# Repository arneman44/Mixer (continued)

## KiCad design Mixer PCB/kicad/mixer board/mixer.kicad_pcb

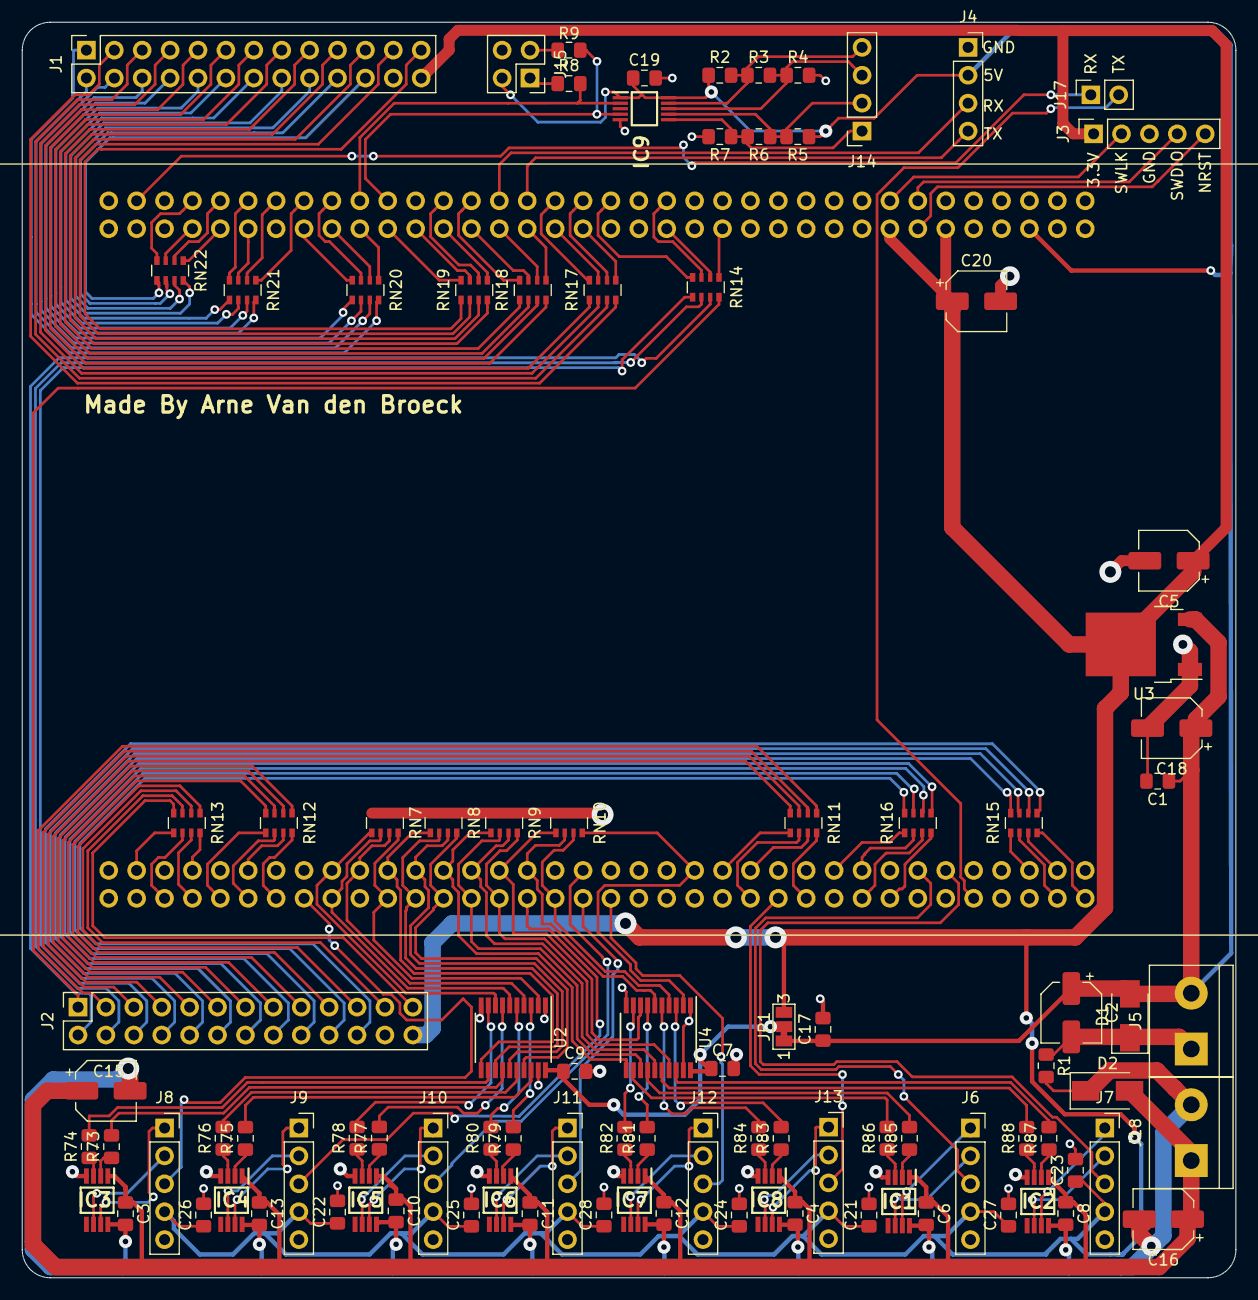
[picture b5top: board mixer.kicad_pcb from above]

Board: 2 copper layers, 110.5 x 114.3 mm, 101 parts (0 on the bottom side), 189 nets.

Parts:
C1, C3, C4, C6, C7, C8, C9, C10, C11, C12, C13, C17, C19, C21, C22, C23, C24, C25, C26, C27, C28: C; C_0805_2012Metric_Pad1.15x1.40mm_HandSolder
C2, C5, C15, C16, C18, C20: CP; CP_Elec_5x5.4
D1, D2: DIODE; D_SMA
IC1, IC2, IC3, IC4, IC5, IC6, IC7, IC8: LB1938FA-BH; SOP65P490X110-8N
IC9: PCA9615DP; SOP50P490X110-10N
J1, J2: Conn_02x13_Odd_Even; PinSocket_2x13_P2.54mm_Vertical
J3, J6, J7, J8, J9, J10, J11, J12, J13: Conn_01x05; PinSocket_1x05_P2.54mm_Vertical
J4: LCD; PinSocket_1x04_P2.54mm_Vertical
J5, J18: Conn_01x02; TerminalBlock_bornier-2_P5.08mm
J14: J; PinSocket_1x04_P2.54mm_Vertical
J15: Conn_02x02_Counter_Clockwise; PinSocket_2x02_P2.54mm_Vertical
J17: Conn_01x02; PinSocket_1x02_P2.54mm_Vertical
JP1: Jumper_3_Bridged12; SolderJumper-3_P1.3mm_Bridged12_Pad1.0x1.5mm_NumberLabels
R1, R8, R9: 4.7K; R_0805_2012Metric_Pad1.15x1.40mm_HandSolder
R2, R4, R5, R7: 390; R_0805_2012Metric_Pad1.15x1.40mm_HandSolder
R3, R6: 100; R_0805_2012Metric_Pad1.15x1.40mm_HandSolder
R73, R74, R75, R76, R77, R78, R79, R80, R81, R82, R83, R84, R85, R86, R87, R88: R; R_0805_2012Metric_Pad1.15x1.40mm_HandSolder
RN7, RN8, RN9, RN10, RN11, RN12, RN13, RN14, RN15, RN16, RN17, RN18, RN19, RN20, RN21, RN22: R_Pack04; R_Array_Convex_4x0603
U1: NUCLEO144-F746ZG; ST_Morpho_Connector_144_STLink_MountingHoles_double
U2, U4: 74HC240; TSSOP-20_4.4x6.5mm_P0.65mm
U3: LD1086DT33TR; TO-252-2

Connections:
+3V3: C5.1, C20.1, C21.1, C22.1, C23.1, C24.1, C25.1, C26.1, C27.1, C28.1, J1.26, J2.26, J3.1, J6.4, J7.4, J8.4, J9.4, J10.4, J11.4, J12.4, J13.4, JP1.3, U1.5, U1.12, U1.16, U1.79, U3.2
+5V: C1.1, C2.1, C17.1, C18.1, C19.1, D1.2, IC9.1, IC9.10, J4.2, J5.2, J15.3, JP1.1, R2.1, R5.1, U1.6, U3.3
Button1: RN14.1, U1.28
Button2: RN11.8, U1.94
Button3: RN11.7, U1.97
Button4: RN11.6, U1.98
Button5: RN11.5, U1.99
Button6: RN12.8, U1.132
Button7: RN12.7, U1.133
Button8: RN12.6, U1.134
Button9: RN14.2, U1.32
Button10: RN14.3, U1.31
Button11: RN14.4, U1.35
Button12: RN15.4, U1.74
Button13: RN15.3, U1.75
Button14: RN15.2, U1.76
Button15: RN15.1, U1.77
Button16: RN16.4, U1.88
DSCL+: IC9.7, J14.2, R5.2, R6.1
DSCL-: IC9.6, J14.1, R6.2, R7.1
DSDA+: IC9.8, J14.3, R3.2, R4.1
DSDA-: IC9.9, J14.4, R2.2, R3.1
Encoder1A: RN20.1, U1.54
Encoder1B: RN17.5, U1.38
Encoder1Button: RN20.2, U1.56
Encoder2A: RN17.6, U1.37
Encoder2B: RN17.7, U1.40
Encoder2Button: RN20.3, U1.55
Encoder3A: RN21.1, U1.57
Encoder3B: RN21.2, U1.59
Encoder3Button: RN20.4, U1.58
Encoder4A: RN18.5, U1.42
Encoder4B: RN18.6, U1.44
Encoder4Button: RN17.8, U1.39
Encoder5A: RN21.3, U1.62
Encoder5B: RN21.4, U1.61
Encoder5Button: RN22.1, U1.64
Encoder6A: RN18.7, U1.46
Encoder6B: RN18.8, U1.45
Encoder6Button: RN22.2, U1.63
Encoder7A: RN19.5, U1.48
Encoder7B: RN19.6, U1.47
Encoder7Button: RN22.3, U1.66
Encoder8A: RN19.7, U1.50
Encoder8B: RN19.8, U1.52
Encoder8Button: RN22.4, U1.65
Fader1: J8.3, U1.130
Fader2: J9.3, U1.114
Fader3: J10.3, U1.109
Fader4: J11.3, U1.110
Fader5: J12.3, U1.108
Fader6: J13.3, U1.96
Fader7: J6.3, U1.85
Fader8: J7.3, U1.83
GND: C1.2, C2.2, C5.2, C7.2, C9.2, C17.2, C18.2, C19.2, C20.2, C21.2, C22.2, C23.2, C24.2, C25.2, C26.2, C27.2, C28.2, D1.1, IC1.4, IC2.4, IC3.4, IC4.4, IC5.4, IC6.4, IC7.4, IC8.4, IC9.5, J1.24, J2.24, J3.3, J4.1, J5.1, J6.5, J7.5, J8.5, J9.5, J10.5, J11.5, J12.5, J13.5, J15.4, R1.1, R4.2, R7.2, RN7.1, RN7.2, RN7.3, RN7.4, RN8.1, RN8.2, RN8.3, RN8.4, RN9.1, RN9.2, RN9.3, RN9.4, RN10.1, RN10.2, RN10.3, RN10.4, U1.8, U1.19, U1.20, U1.22, U1.49, U1.60, U1.71, U1.72, U1.81, U1.92, U1.104, U1.111, U1.126, U1.135, U1.143, U1.144, U2.1, U2.10, U2.19, U3.1, U4.1, U4.10, U4.19
GNDPWR: C3.2, C4.2, C6.2, C8.2, C10.2, C11.2, C12.2, C13.2, C15.2, C16.2, D2.1, IC1.8, IC2.8, IC3.8, IC4.8, IC5.8, IC6.8, IC7.8, IC8.8, J18.2, R1.2
LED1: RN12.5, U1.136
LED2: RN13.8, U1.137
LED3: RN13.7, U1.138
LED4: RN13.6, U1.140
LED5: RN13.5, U1.141
LED6: RN16.3, U1.90
LED7: RN16.2, U1.89
LED8: RN16.1, U1.91
Motor1A: RN7.6, U1.128, U2.6
Motor1A_: R73.2, U2.14
Motor1B: RN7.5, U1.127, U2.8
Motor1B_: R74.2, U2.12
Motor2A: RN7.8, U1.124, U2.2
Motor2A_: R75.2, U2.18
Motor2B: RN7.7, U1.125, U2.4
Motor2B_: R76.2, U2.16
Motor3A: RN8.6, U1.122, U2.13
Motor3A_: R77.2, U2.7
Motor3B: RN8.5, U1.123, U2.11
Motor3B_: R78.2, U2.9
Motor4A: RN8.8, U1.120, U2.17
Motor4A_: R79.2, U2.3
Motor4B: RN8.7, U1.121, U2.15
Motor4B_: R80.2, U2.5
Motor5A: RN9.6, U1.118, U4.13
Motor5A_: R81.2, U4.7
Motor5B: RN9.5, U1.119, U4.11
Motor5B_: R82.2, U4.9
Motor6A: RN9.8, U1.116, U4.17
Motor6A_: R83.2, U4.3
Motor6B: RN9.7, U1.117, U4.15
Motor6B_: R84.2, U4.5
Motor7A: RN10.6, U1.113, U4.6
Motor7A_: R85.2, U4.14
Motor7B: RN10.5, U1.115, U4.8
Motor7B_: R86.2, U4.12
Motor8A: RN10.8, U1.101, U4.2
Motor8A_: R87.2, U4.18
Motor8B: RN10.7, U1.112, U4.4
Motor8B_: R88.2, U4.16
NRST: J3.5, U1.14
unnamed: C7.1, C9.1, JP1.2, U2.20, U4.20
unnamed: IC1.2, R85.1
unnamed: IC1.3, R86.1
unnamed: IC1.6, J6.2
unnamed: IC1.7, J6.1
unnamed: IC2.2, R87.1
unnamed: IC2.3, R88.1
unnamed: IC2.6, J7.2
unnamed: IC2.7, J7.1
unnamed: IC3.2, R73.1
unnamed: IC3.3, R74.1
unnamed: IC3.6, J8.2
unnamed: IC3.7, J8.1
unnamed: IC4.2, R75.1
unnamed: IC4.3, R76.1
unnamed: IC4.6, J9.2
unnamed: IC4.7, J9.1
unnamed: IC5.2, R77.1
unnamed: IC5.3, R78.1
unnamed: IC5.6, J10.2
unnamed: IC5.7, J10.1
unnamed: IC6.2, R79.1
unnamed: IC6.3, R80.1
unnamed: IC6.6, J11.2
unnamed: IC6.7, J11.1
unnamed: IC7.2, R81.1
unnamed: IC7.3, R82.1
unnamed: IC7.6, J12.2
unnamed: IC7.7, J12.1
unnamed: IC8.2, R83.1
unnamed: IC8.3, R84.1
unnamed: IC8.6, J13.2
unnamed: IC8.7, J13.1
unnamed: J1.1, RN20.8
unnamed: J1.2, RN20.7
unnamed: J1.3, RN17.4
unnamed: J1.4, RN20.6
unnamed: J1.5, RN17.3
unnamed: J1.6, RN20.5
unnamed: J1.7, RN17.2
unnamed: J1.8, RN21.8
unnamed: J1.9, RN17.1
unnamed: J1.10, RN21.7
unnamed: J1.11, RN18.4
unnamed: J1.12, RN21.6
unnamed: J1.13, RN18.3
unnamed: J1.14, RN21.5
unnamed: J1.15, RN18.2
unnamed: J1.16, RN22.8
unnamed: J1.17, RN18.1
unnamed: J1.18, RN22.7
unnamed: J1.19, RN19.4
unnamed: J1.20, RN22.6
unnamed: J1.21, RN19.3
unnamed: J1.22, RN22.5
unnamed: J1.23, RN19.2
unnamed: J1.25, RN19.1
unnamed: J2.1, RN14.8
unnamed: J2.2, RN14.7
unnamed: J2.3, RN11.1
unnamed: J2.4, RN14.6
unnamed: J2.5, RN11.2
unnamed: J2.6, RN14.5
unnamed: J2.7, RN11.3
unnamed: J2.8, RN15.5
unnamed: J2.9, RN11.4
unnamed: J2.10, RN15.6
unnamed: J2.11, RN12.1
unnamed: J2.12, RN15.7
unnamed: J2.13, RN12.2
unnamed: J2.14, RN15.8
unnamed: J2.15, RN12.3
unnamed: J2.16, RN16.5
unnamed: J2.17, RN12.4
unnamed: J2.18, RN16.6
unnamed: J2.19, RN13.1
unnamed: J2.20, RN16.7
unnamed: J2.21, RN13.2
unnamed: J2.22, RN16.8
unnamed: J2.23, RN13.3
unnamed: J2.25, RN13.4
unnamed: J15.1, R8.1
unnamed: J15.2, R9.1
RX: J17.1, U1.69
RX4: J4.3, U1.43
SCA1: IC9.2, R8.2, U1.53
SCL1: IC9.4, R9.2, U1.51
SWCLK: J3.2, U1.15
SWDIO: J3.4, U1.13
TX: J17.2, U1.82
TX4: J4.4, U1.41
VPP: C3.1, C4.1, C6.1, C8.1, C10.1, C11.1, C12.1, C13.1, C15.1, C16.1, D2.2, IC1.1, IC2.1, IC3.1, IC4.1, IC5.1, IC6.1, IC7.1, IC8.1, J18.1

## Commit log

2020-06-25 Add kicad files
2020-07-05 Add Gerber's
2020-07-06 Updated Button board to I2C
2020-07-11 add I2C motor driver board
2020-07-11 add I2C splitter board
